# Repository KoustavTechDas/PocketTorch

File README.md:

# LED Control Project

## Overview

This project demonstrates a simple LED control circuit using basic electronic components. It includes an LED, a resistor, a battery, and a switch. The primary goal of this project was to design and create both the schematic and custom PCB layout.

## Components Used

- **LED**: A light-emitting diode that lights up when current flows through it.
- **Resistor**: Limits the current flowing through the LED to prevent damage.
- **Battery**: Provides the power for the circuit.
- **Switch**: Allows the user to turn the LED on and off.

## Design and Layout

In this project, you will learn how to:

1. **Design Schematics**: Create a circuit schematic to outline the connections between the components.
2. **Design Custom PCB Layout**: Develop a custom PCB layout for manufacturing the circuit board.

The design was created using KiCad, following the guidelines and methodologies outlined in the book *KiCad Like a Pro* by Peter Dalmaris. This book is a valuable resource for learning more about PCB design and KiCad software.

## Instructions

1. **Schematic Design**: Create the schematic diagram with the components and their connections.
2. **PCB Layout**: Design the PCB layout based on the schematic, ensuring proper placement and routing of traces.
3. **Manufacturing**: Generate the Gerber files and other necessary files for PCB manufacturing.
4. **Assembly**: Solder the components onto the PCB according to the design.

## Additional Resources

For a more in-depth understanding of PCB design and KiCad, refer to the book *KiCad Like a Pro* by Peter Dalmaris. It provides comprehensive guidance and tips for working with KiCad.

---

Feel free to explore and contribute to this project!

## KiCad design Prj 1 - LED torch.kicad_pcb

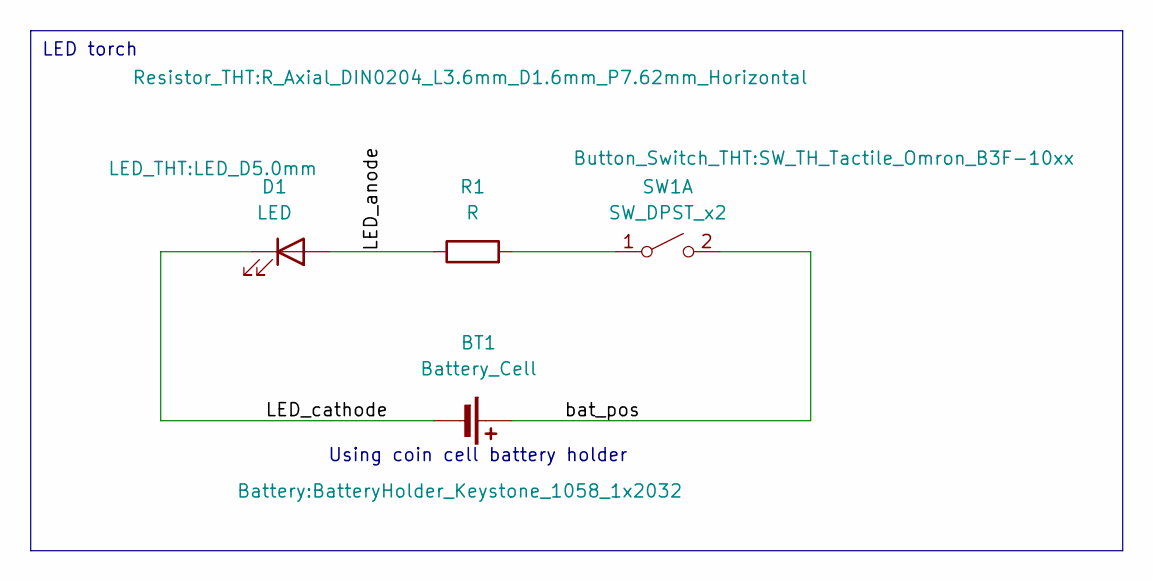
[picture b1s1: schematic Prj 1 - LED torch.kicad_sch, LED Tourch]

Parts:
BT1: Battery_Cell; BatteryHolder_Keystone_1058_1x2032
D1: LED; LED_D5.0mm
R1: R; R_Axial_DIN0204_L3.6mm_D1.6mm_P7.62mm_Horizontal
SW1: SW_DPST_x2; SW_TH_Tactile_Omron_B3F-10xx

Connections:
/LED_anode: D1.2 (A), R1.1
/LED_cathode: BT1.2 (-), D1.1 (K)
/bat_pos: BT1.1 (+), SW1.2 (B)
unnamed: R1.2, SW1.1 (A)

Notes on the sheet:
LED torch
Using coin cell battery holder

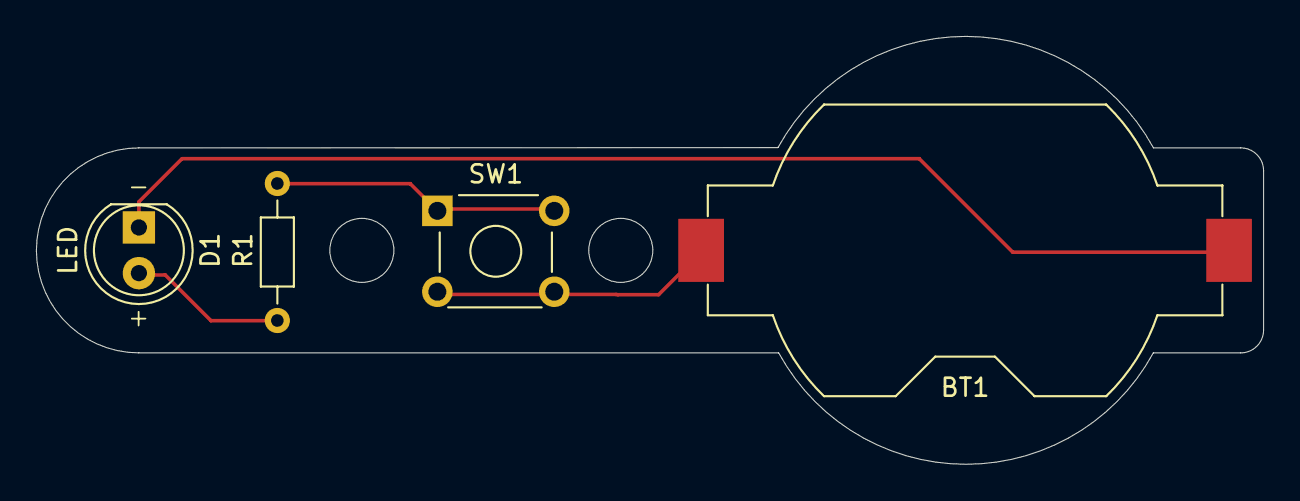
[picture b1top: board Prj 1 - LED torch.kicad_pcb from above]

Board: 2 copper layers, 68.3 x 23.8 mm, 5 parts (1 on the bottom side), 4 nets.

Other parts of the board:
REF1: KiCad-Logo2_8mm_SilkScreen

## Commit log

2024-08-30 "First commit"
